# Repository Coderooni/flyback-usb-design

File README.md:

# Flyback USB Design
## Description
This repository contains files and folders that make up the switch mode power supply (SMPS). It is designed for charging smartphones with a power rating of 20W total. This supply is a dual output USB charger, providing 5V and 2A at each output.

## Instructions
To view the schematic and PCB layout, make sure to install KiCad (I'm using v6.0) and open the files with the _kicad_sch_ and _kicad_pcb_ extensions respectively.

## Future Work
As this is still an initial design, simulation tests are pending before moving forward with PCB manufacturing and assembly.

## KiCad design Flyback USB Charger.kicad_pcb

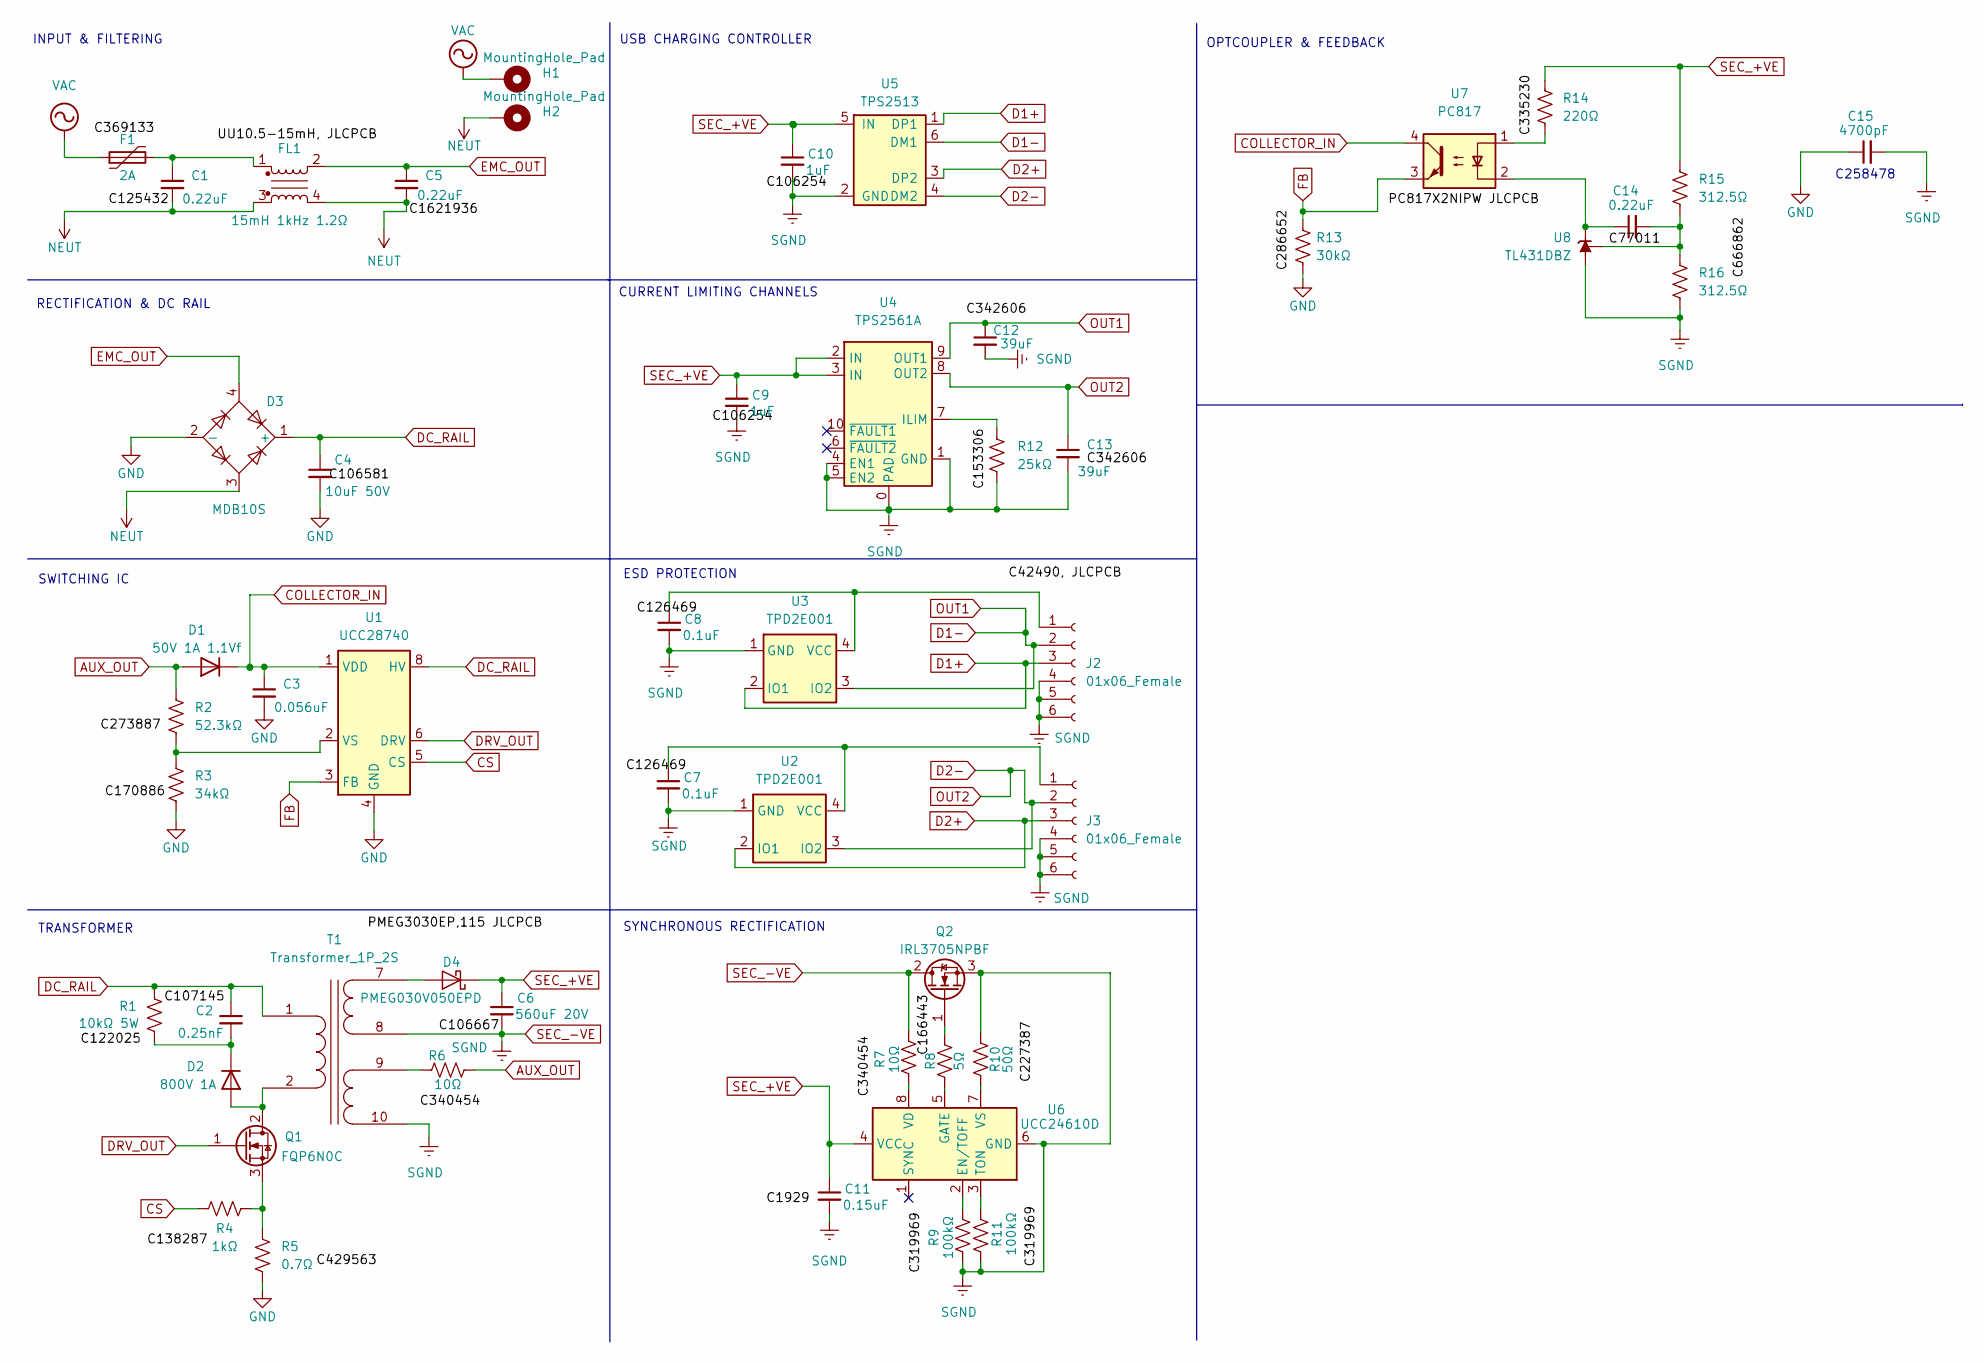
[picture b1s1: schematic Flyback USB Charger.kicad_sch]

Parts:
C1: 0.22uF; C_Rect_L13.0mm_W8.0mm_P10.00mm_FKS3_FKP3_MKS4
C2: 0.25nF; C_0805_2012Metric
C3: 0.056uF; C_0805_2012Metric
C4: 10uF 50V; C_Radial_D10.0mm_H16.0mm_P5.00mm
C5: 0.22uF; C_Radial_D10.0mm_H12.5mm_P5.00mm
C6: 560uF 20V; C_Radial_D12.5mm_H20.0mm_P5.00mm
C7, C8: 0.1uF; C_0805_2012Metric
C9, C10: 1uF; C_01005_0402Metric
C11: 0.15uF; C_1206_3216Metric
C12, C13: 39uF; C_1206_3216Metric
C14: 0.22uF; C_01005_0402Metric
C15: 4700pF; C_0201_0603Metric
D1: 50V 1A 1.1Vf; D_DO-41_SOD81_P10.16mm_Horizontal
D2: 800V 1A; D_DO-41_SOD81_P10.16mm_Horizontal
D3: MDB10S; TSSOP-4_4.4x5mm_P4mm
D4: PMEG030V050EPD; Nexperia_CFP15_SOT-1289
F1: 2A; Fuse_BelFuse_0ZRE0100FF_L18.7mm_W5.1mm
FL1: 15mH 1kHz 1.2Ω; COMMON_MODE CHOKE
H1, H2: MountingHole_Pad; MountingHole_4.3mm_M4_Pad_Via
J2, J3: 01x06_Female; USB_A_SMD_Connector
Q1: FQP6N0C; TO-220-3_Vertical
Q2: IRL3705NPBF; TO-220-3_Vertical
R1: 10kΩ 5W; R_Axial_DIN0617_L17.0mm_D6.0mm_P30.48mm_Horizontal
R2: 52.3kΩ; R_0805_2012Metric
R3: 34kΩ; R_0805_2012Metric
R4: 1kΩ; R_0402_1005Metric
R5: 0.7Ω; R_0805_2012Metric
R6, R7: 10Ω; R_0805_2012Metric
R8: 5Ω; R_0402_1005Metric
R9, R11: 100kΩ; R_0603_1608Metric
R10: 50Ω; R_0402_1005Metric
R12: 25kΩ; R_0805_2012Metric
R13: 30kΩ; R_1206_3216Metric
R14: 220Ω; R_0805_2012Metric
R15, R16: 312.5Ω; R_0603_1608Metric
T1: Transformer_1P_2S; THT_1P1S_Transformer_Bobbin
U1: UCC28740; SOIC-8_3.9x4.9mm_P1.27mm
U2, U3: TPD2E001; SOT-23-4-TPD2E001
U4: TPS2561A; DRC_PACKAGE_TPS2561A
U5: TPS2513; SOT-23-6
U6: UCC24610D; SOIC-8_3.9x4.9mm_P1.27mm
U7: PC817; DIP-4_W7.62mm
U8: TL431DBZ; SOT-23

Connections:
AUX_OUT: D1.2 (A), R2.1, R6.2
COLLECTOR_IN: C3.1, D1.1 (K), U1.1 (VDD), U7.4
CS: R4.1, U1.5 (CS)
D1+: J2.3, U3.2 (IO1), U5.1 (DP1)
D1-: C12.1, J2.2, U3.3 (IO2), U4.9 (OUT1), U5.6 (DM1)
D2+: J3.3, U2.2 (IO1), U5.3 (DP2)
D2-: C13.1, J3.2, U2.3 (IO2), U4.8 (OUT2), U5.4 (DM2)
DC_RAIL: C2.1, C4.1, D3.1 (+), R1.1, T1.1 (AA), U1.8 (HV)
DRV_OUT: Q1.1 (G), U1.6 (DRV)
EMC_OUT: C5.1, D3.4, FL1.2
FB: R13.1, U1.3 (FB), U7.3
GND: C3.2, C4.2, C15.1, D3.2 (-), R3.2, R5.2, R13.2, U1.4 (GND)
NEUT: C1.2, C5.2, D3.3, FL1.3, FL1.4, H2.1
unnamed: C1.1, F1.2, FL1.1
unnamed: C2.2, D2.1 (K), R1.2
unnamed: C7.1, J3.1, U2.4 (VCC)
unnamed: C8.1, J2.1, U3.4 (VCC)
unnamed: C14.1, U7.2, U8.1 (K)
unnamed: C14.2, R15.2, R16.1, U8.2 (REF)
unnamed: D2.2 (A), Q1.2 (D), T1.2 (AB)
unnamed: D4.1 (A), D4.2 (A), T1.7 (SA)
unnamed: Q1.3 (S), R4.2, R5.1
unnamed: Q2.1 (G), R8.2
unnamed: R2.2, R3.1, U1.2 (VS)
unnamed: R6.1, T1.9 (SC)
unnamed: R7.1, U6.8 (VD)
unnamed: R8.1, U6.5 (GATE)
unnamed: R9.2, U6.2 (EN/TOFF)
unnamed: R10.1, U6.7 (VS)
unnamed: R11.2, U6.3 (TON)
unnamed: R12.1, U4.7 (ILIM)
unnamed: R14.2, U7.1
SEC_+VE: C6.1, C9.1, C10.1, C11.1, D4.3 (K), R14.1, R15.1, U4.2 (IN), U4.3 (IN), U5.5 (IN), U6.4 (VCC)
SEC_-VE: C6.2, C7.2, C8.2, C9.2, C10.2, C11.2, C12.2, C13.2, C15.2, J2.4, J2.5, J2.6, J3.4, J3.5, J3.6, Q2.2 (D), Q2.3 (S), R7.2, R9.1, R10.2, R11.1, R12.2, R16.2, T1.8 (SB), T1.10 (SD), U2.1 (GND), U3.1 (GND), U4.0 (PAD), U4.1 (GND), U4.4 (EN1), U4.5 (EN2), U5.2 (GND), U6.6 (GND), U8.3 (A)
VAC: F1.1, H1.1

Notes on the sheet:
USB CHARGING CONTROLLER
OPTCOUPLER & FEEDBACK
TRANSFORMER
SWITCHING IC
ESD PROTECTION
INPUT & FILTERING
CURRENT LIMITING CHANNELS
RECTIFICATION & DC RAIL
C258478
SYNCHRONOUS RECTIFICATION

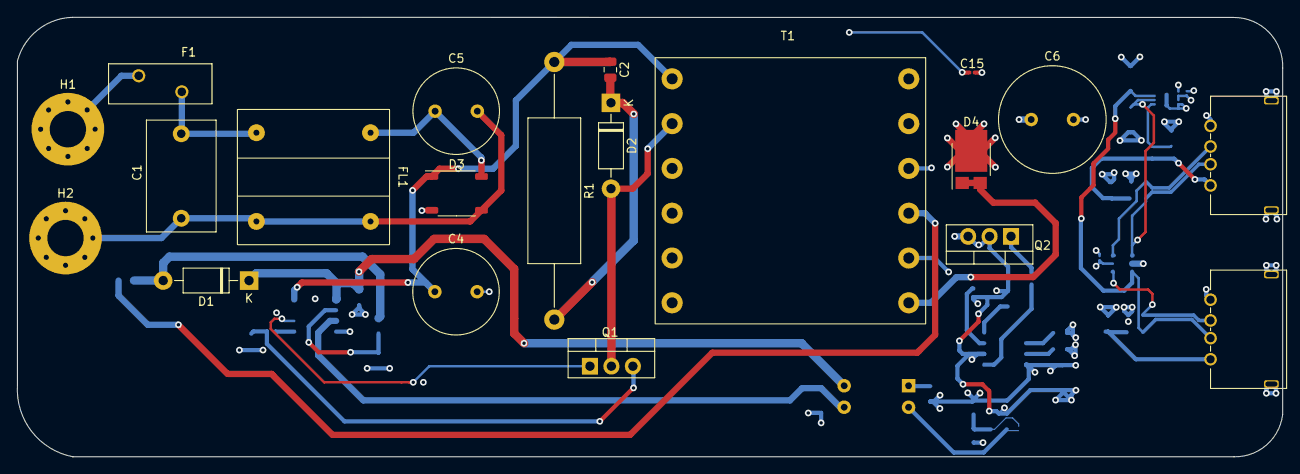
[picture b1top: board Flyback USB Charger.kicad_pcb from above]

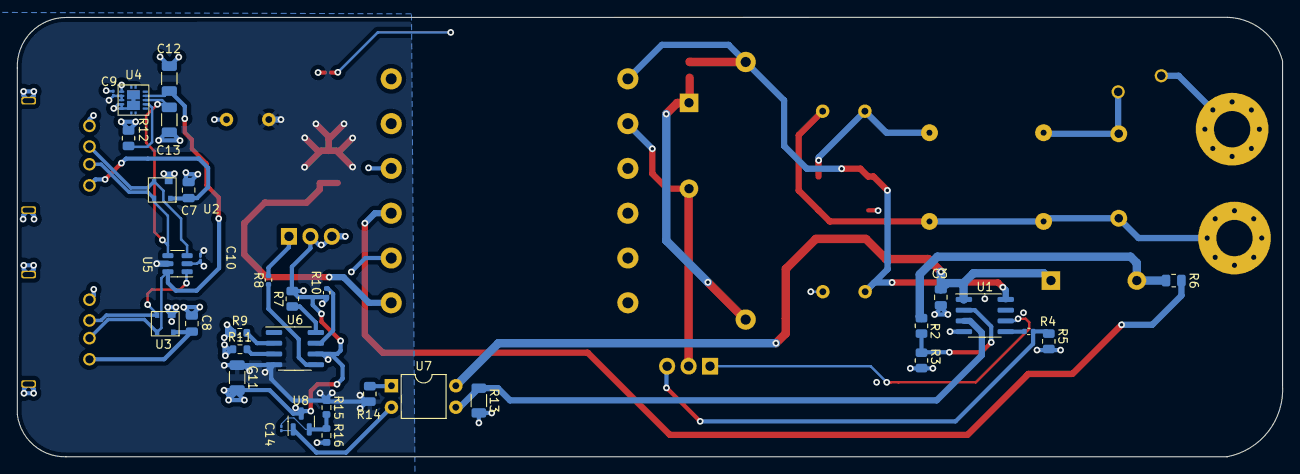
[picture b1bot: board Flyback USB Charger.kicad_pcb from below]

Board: 4 copper layers, 149.7 x 52.0 mm, 52 parts (32 on the bottom side), 35 nets.

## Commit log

2022-12-16 Should be my first commit to the flyback usb design repo
2022-12-16 Added a README file
2023-10-25 Added code files to the directory
2023-10-25 Added comments to the function
2023-10-25 Updated comments
